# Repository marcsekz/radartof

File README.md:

## Fun stuff:
- USB descriptor will always fail on CM4, as that core does not have access to the memory area containing the device ID. Mitigated with fixed ID.
- UART4 is connected in reverse to STDC14 debug connector (whoopsie)
-

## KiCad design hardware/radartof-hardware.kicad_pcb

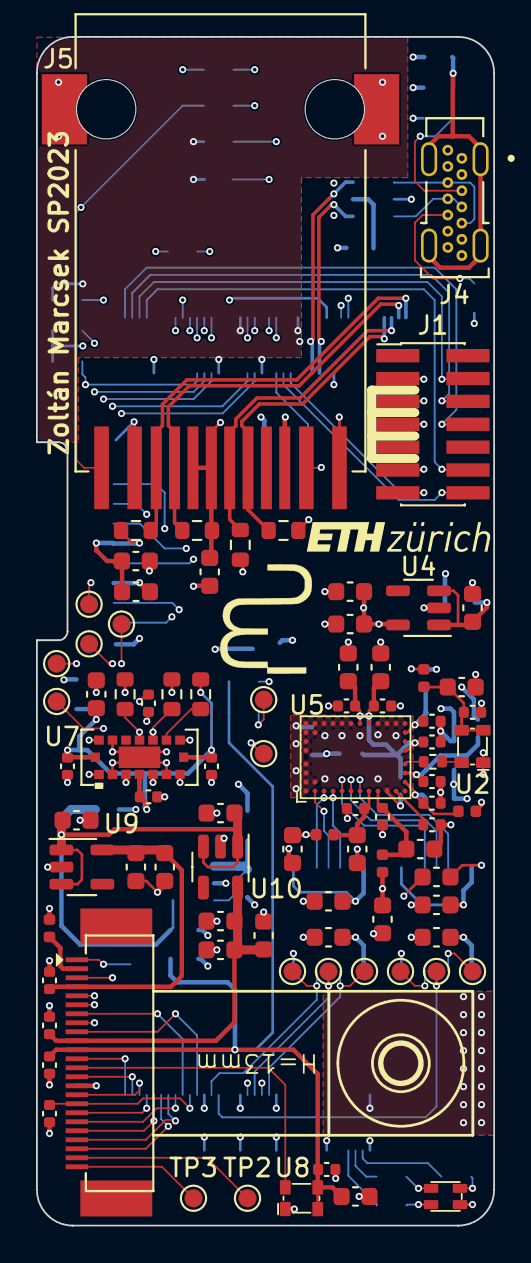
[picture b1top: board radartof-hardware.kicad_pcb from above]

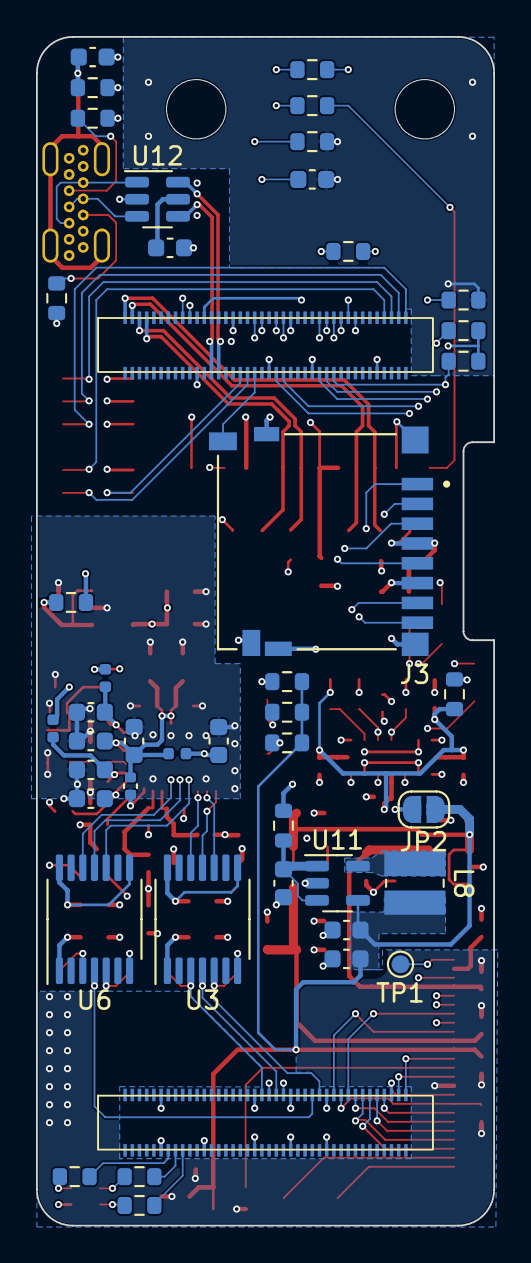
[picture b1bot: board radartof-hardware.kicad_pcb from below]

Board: 6 copper layers, 25.4 x 66.0 mm, 130 parts (44 on the bottom side), 95 nets.

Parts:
C1, C4, C12, C18, C19, C26, C27, C32, C36, C37, C38, C42, C43, C44, C46, C47, C48, C50, C61: 10u; C_0603_1608Metric
C2, C5, C7, C9, C14, C16, C21, C23, C45: 1u; C_0603_1608Metric
C3, C6, C8, C10, C13, C15, C17, C20, C22, C24: 10n; C_0402_1005Metric
C11, C34, C49, C51, C53, C57, C58, C59, C60: 100n; C_0603_1608Metric
C25: 470n; C_0402_1005Metric
C28: 4u7; C_0603_1608Metric
C29, C30, C31, C33, C39, C40, C41, C55: 100n; C_0402_1005Metric
C35: 22p; C_0402_1005Metric
C54: 1n; C_0603_1608Metric
D1: Würth 150066M153000; Würth_150066M153000
J1: Debug; PinHeader_2x07_P1.27mm_Vertical_SMD
J2: Camera; OV2640FSL
J3: 1140084168; AMPHENOL_1140084168
J4: FS USB; MOLEX_216989-0001
J5: J3026G01DNLT; PE_J3026G01DNLT
JP2: 3v3 Select; SolderJumper-2_P1.3mm_Open_RoundedPad1.0x1.5mm
L1, L2, L3, L4, L5, L6, L7, L9: BLM15PX471SZ1D; L_0402_1005Metric
L8: 74438336022; L_Wuerth_MAPI-3020
R1: 150; R_0402_1005Metric
R2, R3, R10, R11: 2k2; R_0603_1608Metric
R4, R5, R6, R7: 47k; R_0603_1608Metric
R8, R9: 10k; R_0603_1608Metric
R12, R13, R14, R15: 49.9; R_0603_1608Metric
R16, R17: 5k1; R_0603_1608Metric
R18, R19, R26: 470; R_0603_1608Metric
R20: 1M; R_0603_1608Metric
R21, R22, R23, R24: 0; R_0603_1608Metric
R25: 1k; R_0603_1608Metric
R27: 220; R_0603_1608Metric
TP1: Strobe; TestPoint_Pad_D1.0mm
TP2: Vmotor; TestPoint_Pad_D1.0mm
TP3: GNDmotor; TestPoint_Pad_D1.0mm
TP4: MOSI; TestPoint_Pad_D1.0mm
TP5: SCK; TestPoint_Pad_D1.0mm
TP6: RADAR_INT; TestPoint_Pad_D1.0mm
TP7: NSS; TestPoint_Pad_D1.0mm
TP8: RADAR_nRST; TestPoint_Pad_D1.0mm
TP9: MISO; TestPoint_Pad_D1.0mm
TP10: TOF_LPn; TestPoint_Pad_D1.0mm
TP11: SCL3; TestPoint_Pad_D1.0mm
TP12: SDA3; TestPoint_Pad_D1.0mm
TP13: TOF_INT; TestPoint_Pad_D1.0mm
TP14: TOF_RST; TestPoint_Pad_D1.0mm
TP15: SDA1; TestPoint_Pad_D1.0mm
TP16: SCL1; TestPoint_Pad_D1.0mm
U1: DF40HC(3.5)-80DS-0.4V(51); MODULE_ABX00042_NOSCREWS
U2: KC2016Z80.0000; KC2016Z
U3, U6: TXU0304; TSSOP-14_4.4x5mm_P0.65mm
U4: TLV74318 SOT23-5; SOT-23-5
U5: BGT60UTR13DAiP
U7: VL53L5CXV0GC/1; VL53L5CXV0GC&slash_1
U8: KC2016Z24.0000; KC2016Z
U9: TLV74328 SOT23-5; SOT-23-5
U10: TLV74315 SOT23-5; SOT-23-5
U11: LM3671MF-3.3; TSOT-23-5
U12: USBLC6-2SC6; SOT-23-6

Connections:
+1V5: C40.1, C43.1, C44.1, C45.1, J2.10, U10.5 (OUT)
+1V8: C4.1, C11.1, C18.1, C27.1, C58.1, C60.1, C61.1, L2.1, L3.1, L4.1, L5.1, L6.1, L7.1, U3.8 (OE), U3.14 (VCCB), U4.5 (OUT), U6.8 (OE), U6.14 (VCCB)
+2V8: C37.1, C38.1, C39.1, J2.4, U9.5 (OUT)
+3.3V: C49.1, C50.1, C51.1, C55.1, D1.4 (A), J1.3 (VCC), J3.4 (VDD), J5.5 (TCT), J5.6 (RCT), J5.12, JP2.2 (B), R2.1, R3.1, R4.1, R5.1, R12.1, R13.1, R14.1, R15.1, R23.1, R24.1, U1.J1_72 (V-SDCARD), U1.J2_23 (VCC/+3V3), U1.J2_34 (VCC), U1.J2_43 (VCC/+3V3), U1.J2_69 (VCC/+3V3)
+5V: R22.1, U1.J1_23 (USB1_VBUS)
/Camera/5v_tof: C46.1, R22.2, U11.1 (Vin), U11.3 (EN)
/Camera/CAM_CK: C35.1, J2.17, U1.J2_20 (CAM_CLK)
/Camera/CAM_D0: J2.19, U1.J2_16 (CAM_D0)
/Camera/CAM_D1: J2.21, U1.J2_14 (CAM_D1)
/Camera/CAM_D2: J2.22, U1.J2_12 (CAM_D2)
/Camera/CAM_D3: J2.20, U1.J2_10 (CAM_D3)
/Camera/CAM_D4: J2.18, U1.J2_8 (CAM_D4)
/Camera/CAM_D5: J2.16, U1.J2_6 (CAM_D5)
/Camera/CAM_D6: J2.14, U1.J2_4 (CAM_D6)
/Camera/CAM_D7: J2.12, U1.J2_2 (CAM_D7)
/Camera/CAM_HS: J2.9, U1.J2_22 (CAM_HS)
/Camera/CAM_PWDN: J2.8, R9.1, U1.J1_37 (UART1_RTS)
/Camera/CAM_VS: J2.7, U1.J2_18 (CAM_VS)
/Camera/CAM_nRST: C34.1, J2.6, R8.2, U1.J1_39 (UART1_CTS)
/Camera/GNDMotor: J2.24, TP3.1
/Camera/I2C1_SCL: J2.5, R11.2, TP16.1, U1.J1_45 (I2C1_SCL)
/Camera/I2C1_SDA: J2.3, R10.2, TP15.1, U1.J1_43 (I2C1_SDA)
/Camera/LX: L8.1, U11.5 (SW)
/Camera/STROBE: J2.1, TP1.1
/Camera/Vmotor: J2.23, TP2.1
/Camera/XCLK: J2.13, U8.3 (CLK)
/Connectors/ETH_A+: J5.3 (TD+), R12.2, U1.J1_1 (ETH_A+)
/Connectors/ETH_A-: J5.4 (TD-), R13.2, U1.J1_3 (ETH_A-)
/Connectors/ETH_B+: J5.7 (RD+), R14.2, U1.J1_5 (ETH_B+)
/Connectors/ETH_B-: J5.8 (RD-), R15.2, U1.J1_7 (ETH_B-)
/Connectors/ETH_LED1: R19.1, U1.J1_17 (ETH_L1)
/Connectors/ETH_LED2: R18.1, U1.J1_19 (ETH_L2)
/Connectors/USB_FS+: U1.J1_26 (USB0_D+), U12.4 (I/O2)
/Connectors/USB_FS-: U1.J1_28 (USB0_D-), U12.6 (I/O1)
/Connectors/USB_Shield: C54.1, J4.S1 (SHIELD), R20.1
/Connectors/conn_USB+: J4.A7 (D-), J4.B7 (D-), U12.1 (I/O1)
/Connectors/conn_USB-: J4.A6 (D+), J4.B6 (D+), U12.3 (I/O2)
/Portenta/CATB: D1.3 (BK), R27.2
/Portenta/CATG: D1.2 (GK), R26.2
/Portenta/CATR: D1.1 (RK), R25.2
/Portenta/I2C3_SCL: R2.2, TP11.1, U1.J1_46 (I2C0_SCL), U7.C4 (SCL)
/Portenta/I2C3_SDA: R3.2, TP12.1, U1.J1_44 (I2C0_SDA), U7.C3 (SDA)
/Portenta/RADAR_INT: TP6.1, U1.J2_26 (UART2_TX), U3.5 (A4Y)
/Portenta/RADAR_nRST: TP8.1, U1.J2_28 (UART2_RX), U6.4 (A3)
/Portenta/SDC_CD: J3.9 (DET_B), U1.J1_38 (UART0_RTS)
/Portenta/SDC_CLK: J3.5 (CLK), U1.J1_55 (SDC_CLK)
/Portenta/SDC_CMD: J3.3 (CMD), U1.J1_57 (SDC_CMD)
/Portenta/SDC_D0: J3.7 (DAT0), U1.J1_59 (SDC_D0)
/Portenta/SDC_D1: J3.8 (DAT1), U1.J1_61 (SDC_D1)
/Portenta/SDC_D2: R21.1, U1.J1_63 (SDC_D2)
/Portenta/SDC_D3: J3.2 (DAT3/CD), U1.J1_65 (SDC_D3)
/Portenta/SPI2_MISO: TP9.1, U1.J2_40 (SPI1_MISO), U6.5 (A4Y)
/Portenta/SPI2_MOSI: TP4.1, U1.J2_42 (SPI1_MOSI), U3.3 (A2)
/Portenta/SPI2_NSS: TP7.1, U1.J2_36 (SPI1_CS), U6.3 (A2)
/Portenta/SPI2_SCK: TP5.1, U1.J2_38 (SPI1_CK), U3.4 (A3)
/Portenta/SWCLK: J1.6 (JCLK/SWCLK), U1.J1_77 (SWCK)
/Portenta/SWDIO: J1.4 (JTMS/SWDIO), U1.J1_75 (SWDIO)
/Portenta/SWO: J1.8 (JTDO/SWO), U1.J1_79 (SWO)
/Portenta/TOF_INT: R4.2, TP13.1, U1.J1_58 (I2S_WS), U7.A3 (INT)
/Portenta/TOF_LPn: R5.2, TP10.1, U1.J1_60 (I2S_DI), U7.A5 (LPn)
/Portenta/TOF_RST: R7.1, TP14.1, U1.J1_56 (I2S_MCK), U7.A1 (I2C_RST)
/Portenta/UART4_RX: J1.14 (VCP_TX), U1.J1_36 (UART0_RX)
/Portenta/UART4_TX: J1.13 (VCP_RX), U1.J1_34 (UART0_TX)
/Portenta/nLEDB: R27.1, U1.J2_67 (PWM_5)
/Portenta/nLEDG: R26.1, U1.J2_65 (PWM_4)
/Portenta/nLEDR: R25.1, U1.J2_63 (PWM_3)
/Portenta/nRST: J1.12 (~RST), U1.J1_73 (~RESET)
/Radar/80mhz: R1.1, U2.3 (CLK)
/Radar/INT_1V8: U3.10 (B4), U5.C1 (IRQ)
/Radar/MISO_1V8: U5.E1 (MISO), U6.10 (B4)
/Radar/MOSI_1V8: U3.12 (B2Y), U5.D1 (MOSI)
/Radar/NSS_1V8: U5.G1 (~CS), U6.12 (B2Y)
/Radar/OSC_CLK: R1.2, U5.M4 (OSC_CLK)
/Radar/RST_1V8: U5.F1 (RST), U6.11 (B3Y)
/Radar/SCK_1V8: U3.11 (B3Y), U5.B1 (CLK)
/Radar/VDD_A: C12.1, C13.1, L4.2, U5.J1 (VDD_{A})
/Radar/VDD_D: C5.1, C6.1, L2.2, U5.H1 (VDD_{D})
/Radar/VDD_LF: C2.1, C3.1, L1.2, U5.M2 (VDD_{LF})
/Radar/VDD_PLL: C14.1, C15.1, L5.2, U5.M3 (VDD_{PLL})
/Radar/VDD_RF: C7.1, C8.1, C16.1, C17.1, C19.1, C20.1, C23.1, C24.1, L6.2, U5.G8 (VDD_{RF}), U5.H8 (VDD_{RF}), U5.M5 (VDD_{RF})
/Radar/VDD_VCO: C21.1, C22.1, L7.2, U5.M7 (VDD_{VCO})
/Radar/V_AREF: C25.1, U5.L1 (V_{AREF})
/Radar/V_OSC: C9.1, C10.1, L3.2, U2.1 (INH), U2.4 (VCC)
/ToF Sensor/RSVD6: R6.2, U7.C2 (RSVD6)
GND: C1.2, C2.2, C3.2, C4.2, C5.2, C6.2, C7.2, C8.2, C9.2, C10.2, C11.2, C12.2, C13.2, C14.2, C15.2, C16.2, C17.2, C18.2, C19.2, C20.2, C21.2, C22.2, C23.2, C24.2, C25.2, C26.2, C27.2, C28.2, C29.2, C30.2, C31.2, C32.2, C33.2, C34.2, C35.2, C36.2, C37.2, C38.2, C39.2, C40.2, C41.2, C42.2, C43.2, C44.2, C45.2, C46.2, C47.2, C48.2, C49.2, C50.2, C51.2, C53.2, C54.2, C55.2, C57.2, C58.2, C59.2, C60.2, C61.2, J1.5 (GND), J1.7 (GND), J1.11 (GNDDetect), J2.15, J3.6 (VSS), J3.10 (DET_A), J3.11 (SHIELD), J4.A1 (GND), J4.A12 (GND), J4.B1 (GND), J4.B12 (GND), J5.2, J5.10, J5.S1 (SHIELD), J5.S2 (SHIELD), L9.1, R7.2, R9.2, R16.1, R17.1, R20.2, U1.J1_22 (GND), U1.J1_31 (GND), U1.J1_42 (GND), U1.J1_47 (GND), U1.J1_54 (GND), U1.J2_24 (GND_1), U1.J2_33 (GND_1), U1.J2_44 (GND_1), U1.J2_57 (GND_1), U1.J2_70 (GND_1), U2.2 (GND), U3.7 (GND), U4.2 (GND), U5.A1 (VSS_{RF}), U5.A2 (VSS_{D}), U5.A3 (VSS_{D}), U5.A4 (VSS_{RF}), U5.A5 (VSS_{RF}), U5.A6 (VSS_{RF}), U5.A7 (VSS_{RF}), U5.A8 (VSS_{RF}), U5.B2 (VSS_{RF}), U5.B7 (VSS_{RF}), U5.B8 (VSS_{RF}), U5.C8 (VSS_{RF}), U5.D8 (VSS_{RF}), U5.E8 (VSS_{RF}), U5.F8 (VSS_{RF}), U5.J8 (VSS_{RF}), U5.K1 (VSS_{A}), U5.K8 (VSS_{RF}), U5.L8 (VSS_{RF}), U5.M1 (VSS_{RF}), U5.M8 (VSS_{RF}), U6.7 (GND), U7.A2 (RSVD4), U7.A6 (RSVD1), U7.A7 (RSVD2), U7.B4 (THERMAL_PAD), U7.C1 (GND), U7.C6 (RSVD3), U7.C7 (GND), U8.2 (GND), U9.2 (GND), U10.2 (GND), U11.2 (GND), U12.2 (GND)
GNDA: J2.2, L9.2
unnamed: J3.1 (DAT2), R21.2
unnamed: J4.A5 (CC1), R16.2
unnamed: J4.B5 (CC2), R17.2
unnamed: J5.1, R18.2
unnamed: J5.11, R19.2
unnamed: C53.1, U12.5 (VBUS)
VCAM: C32.1, C33.1, C36.1, C41.1, C42.1, C47.1, C48.1, J2.11, JP2.1 (A), L8.2, R8.1, R10.1, R11.1, U8.1 (INH), U8.4 (VCC), U9.1 (IN), U9.3 (EN), U10.1 (IN), U10.3 (EN), U11.4 (FB)
VTOF: C28.1, C29.1, C30.1, C31.1, R6.1, R24.2, U7.A4 (IOVDD), U7.B1 (AVDD), U7.B7 (AVDD)
Vradar: C1.1, C26.1, C57.1, C59.1, L1.1, R23.2, U3.1 (VCCA), U4.1 (IN), U4.3 (EN), U6.1 (VCCA)

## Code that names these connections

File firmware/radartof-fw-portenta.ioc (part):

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Mcu.Name=STM32H747XIHx
Mcu.Package=TFBGA240
Mcu.UserName=STM32H747XIHx
PA0.GPIOParameters=PinAttribute
PA0.Mode=Asynchronous
PA0.PinAttribute=CortexM4
PA0.Signal=UART4_TX
PA1.GPIOParameters=GPIO_Speed,PinAttribute
PA1.GPIO_Speed=GPIO_SPEED_FREQ_VERY_HIGH
PA1.Mode=RMII
PA1.PinAttribute=CortexM7
PA1.Signal=ETH_REF_CLK
PA11.GPIOParameters=PinAttribute
PA11.Mode=Device_Only
PA11.PinAttribute=CortexM4
PA11.Signal=USB_OTG_FS_DM
PA12.GPIOParameters=PinAttribute
PA12.Mode=Device_Only
PA12.PinAttribute=CortexM4
PA12.Signal=USB_OTG_FS_DP
PA13\ (JTMS/SWDIO).GPIOParameters=PinAttribute
PA13\ (JTMS/SWDIO).Mode=Serial_Wire
PA13\ (JTMS/SWDIO).PinAttribute=CortexM7
PA13\ (JTMS/SWDIO).Signal=DEBUG_JTMS-SWDIO
PA14\ (JTCK/SWCLK).GPIOParameters=PinAttribute
PA14\ (JTCK/SWCLK).Mode=Serial_Wire
PA14\ (JTCK/SWCLK).PinAttribute=CortexM7
PA14\ (JTCK/SWCLK).Signal=DEBUG_JTCK-SWCLK
PA2.GPIOParameters=GPIO_Speed,PinAttribute
PA2.GPIO_Speed=GPIO_SPEED_FREQ_VERY_HIGH
PA2.Mode=RMII
PA2.PinAttribute=CortexM7
PA2.Signal=ETH_MDIO
PA3.GPIOParameters=PinAttribute
PA3.Mode=Device_HS
PA3.PinAttribute=CortexM7
PA3.Signal=USB_OTG_HS_ULPI_D0
PA4.GPIOParameters=PinAttribute
PA4.Mode=Slave_8_bits_External_Synchro
PA4.PinAttribute=CortexM4
PA4.Signal=DCMI_HSYNC
PA5.GPIOParameters=PinAttribute
PA5.Mode=Device_HS
PA5.PinAttribute=CortexM7
PA5.Signal=USB_OTG_HS_ULPI_CK
PA6.GPIOParameters=PinAttribute
PA6.Mode=Slave_8_bits_External_Synchro
PA6.PinAttribute=CortexM4
PA6.Signal=DCMI_PIXCLK
PA7.GPIOParameters=GPIO_Speed,PinAttribute
PA7.GPIO_Speed=GPIO_SPEED_FREQ_VERY_HIGH
PA7.Mode=RMII
PA7.PinAttribute=CortexM7
PA7.Signal=ETH_CRS_DV
PA8.GPIOParameters=GPIO_Label,PinAttribute
PA8.GPIO_Label=TOF_PWREN
PA8.PinAttribute=Free
PA8.Signal=GPIO_Output
PB0.GPIOParameters=PinAttribute
PB0.Mode=Device_HS
PB0.PinAttribute=CortexM7
PB0.Signal=USB_OTG_HS_ULPI_D1
PB1.GPIOParameters=PinAttribute
PB1.Mode=Device_HS
PB1.PinAttribute=CortexM7
PB1.Signal=USB_OTG_HS_ULPI_D2
PB10.GPIOParameters=PinAttribute
PB10.Mode=Device_HS
PB10.PinAttribute=CortexM7
PB10.Signal=USB_OTG_HS_ULPI_D3
PB11.GPIOParameters=PinAttribute
PB11.Mode=Device_HS
PB11.PinAttribute=CortexM7
PB11.Signal=USB_OTG_HS_ULPI_D4
PB12.GPIOParameters=PinAttribute
PB12.Mode=Device_HS
PB12.PinAttribute=CortexM7
PB12.Signal=USB_OTG_HS_ULPI_D5
PB13.GPIOParameters=PinAttribute
PB13.Mode=Device_HS
PB13.PinAttribute=CortexM7
PB13.Signal=USB_OTG_HS_ULPI_D6
PB14.GPIOParameters=PinAttribute
PB14.Mode=SD_4_bits_Wide_bus
PB14.PinAttribute=CortexM7
PB14.Signal=SDMMC2_D0
PB15.GPIOParameters=PinAttribute
PB15.Mode=SD_4_bits_Wide_bus
PB15.PinAttribute=CortexM7
PB15.Signal=SDMMC2_D1
PB3\ (JTDO/TRACESWO).GPIOParameters=PinAttribute
PB3\ (JTDO/TRACESWO).Mode=SD_4_bits_Wide_bus
PB3\ (JTDO/TRACESWO).PinAttribute=CortexM7
PB3\ (JTDO/TRACESWO).Signal=SDMMC2_D2
PB4\ (NJTRST).GPIOParameters=PinAttribute
PB4\ (NJTRST).Mode=SD_4_bits_Wide_bus
PB4\ (NJTRST).PinAttribute=CortexM7
PB4\ (NJTRST).Signal=SDMMC2_D3
PB5.GPIOParameters=PinAttribute
PB5.Mode=Device_HS
PB5.PinAttribute=CortexM7
PB5.Signal=USB_OTG_HS_ULPI_D7
PB6.GPIOParameters=PinAttribute
PB6.Mode=I2C
PB6.PinAttribute=CortexM7
PB6.Signal=I2C1_SCL
PB7.GPIOParameters=PinAttribute
PB7.Mode=I2C
PB7.PinAttribute=CortexM7
PB7.Signal=I2C1_SDA
PB9.ContextOwner=CortexM4
PB9.GPIOParameters=GPIO_Label,PinAttribute
PB9.GPIO_Label=TOF_INT
PB9.PinAttribute=CortexM4
PB9.Signal=GPIO_Input
PC0.GPIOParameters=PinAttribute
PC0.Mode=Device_HS
PC0.PinAttribute=CortexM7
PC0.Signal=USB_OTG_HS_ULPI_STP
PC1.GPIOParameters=GPIO_Speed,PinAttribute
PC1.GPIO_Speed=GPIO_SPEED_FREQ_VERY_HIGH
PC1.Mode=RMII
PC1.PinAttribute=CortexM7
PC1.Signal=ETH_MDC
PC14-OSC32_IN\ (OSC32_IN).GPIOParameters=PinAttribute
PC14-OSC32_IN\ (OSC32_IN).Mode=LSE-External-Clock-Source
PC14-OSC32_IN\ (OSC32_IN).PinAttribute=Free
PC14-OSC32_IN\ (OSC32_IN).Signal=RCC_OSC32_IN
PC2.GPIOParameters=PinAttribute
PC2.Mode=Full_Duplex_Master
PC2.PinAttribute=CortexM4
PC2.Signal=SPI2_MISO
PC3.GPIOParameters=PinAttribute
PC3.Mode=Full_Duplex_Master
PC3.PinAttribute=CortexM4
PC3.Signal=SPI2_MOSI
PC4.GPIOParameters=GPIO_Speed,PinAttribute
PC4.GPIO_Speed=GPIO_SPEED_FREQ_VERY_HIGH
PC4.Mode=RMII
PC4.PinAttribute=CortexM7
PC4.Signal=ETH_RXD0
PC5.GPIOParameters=GPIO_Speed,PinAttribute
PC5.GPIO_Speed=GPIO_SPEED_FREQ_VERY_HIGH
PC5.Mode=RMII
PC5.PinAttribute=CortexM7
PC5.Signal=ETH_RXD1
PD0.GPIOParameters=PinAttribute
PD0.PinAttribute=CortexM7
PD0.Signal=FMC_D2_DA2
PD1.GPIOParameters=PinAttribute
PD1.PinAttribute=CortexM7
PD1.Signal=FMC_D3_DA3
PD10.GPIOParameters=PinAttribute
PD10.PinAttribute=CortexM7
PD10.Signal=FMC_D15_DA15
PD11.GPIOParameters=PinAttribute
PD11.Mode=Single Bank 1
PD11.PinAttribute=CortexM7
PD11.Signal=QUADSPI_BK1_IO0
PD12.GPIOParameters=PinAttribute
PD12.Mode=Single Bank 1
PD12.PinAttribute=CortexM7
PD12.Signal=QUADSPI_BK1_IO1
PD13.GPIOParameters=PinAttribute
PD13.Mode=Single Bank 1
PD13.PinAttribute=CortexM7
PD13.Signal=QUADSPI_BK1_IO3
PD14.GPIOParameters=PinAttribute
PD14.PinAttribute=CortexM7
PD14.Signal=FMC_D0_DA0
PD15.GPIOParameters=PinAttribute
PD15.PinAttribute=CortexM7
PD15.Signal=FMC_D1_DA1
PD3.GPIOParameters=GPIO_Label,PinAttribute
PD3.GPIO_Label=TOF_RST
PD3.PinAttribute=Free
PD3.Signal=GPIO_Output
PD6.GPIOParameters=PinAttribute
PD6.Mode=SD_4_bits_Wide_bus
PD6.PinAttribute=CortexM7
PD6.Signal=SDMMC2_CK
PD7.GPIOParameters=PinAttribute
PD7.Mode=SD_4_bits_Wide_bus
PD7.PinAttribute=CortexM7
PD7.Signal=SDMMC2_CMD
PD8.GPIOParameters=PinAttribute
PD8.PinAttribute=CortexM7
PD8.Signal=FMC_D13_DA13
PD9.GPIOParameters=PinAttribute
PD9.PinAttribute=CortexM7
PD9.Signal=FMC_D14_DA14
PE0.GPIOParameters=PinAttribute
PE0.PinAttribute=CortexM7
PE0.Signal=FMC_NBL0
PE1.GPIOParameters=PinAttribute
PE1.PinAttribute=CortexM7
PE1.Signal=FMC_NBL1
PE10.GPIOParameters=PinAttribute
PE10.PinAttribute=CortexM7
PE10.Signal=FMC_D7_DA7
PE11.GPIOParameters=PinAttribute
PE11.PinAttribute=CortexM7
PE11.Signal=FMC_D8_DA8
PE12.GPIOParameters=PinAttribute
PE12.PinAttribute=CortexM7
PE12.Signal=FMC_D9_DA9
PE13.GPIOParameters=PinAttribute
PE13.PinAttribute=CortexM7
PE13.Signal=FMC_D10_DA10
PE14.GPIOParameters=PinAttribute
PE14.PinAttribute=CortexM7
PE14.Signal=FMC_D11_DA11
PE15.GPIOParameters=PinAttribute
PE15.PinAttribute=CortexM7
PE15.Signal=FMC_D12_DA12
PE7.GPIOParameters=PinAttribute
PE7.PinAttribute=CortexM7
PE7.Signal=FMC_D4_DA4
PE8.GPIOParameters=PinAttribute
PE8.PinAttribute=CortexM7
PE8.Signal=FMC_D5_DA5
PE9.GPIOParameters=PinAttribute
PE9.PinAttribute=CortexM7
PE9.Signal=FMC_D6_DA6
PF0.GPIOParameters=PinAttribute
PF0.PinAttribute=CortexM7
PF0.Signal=FMC_A0
PF1.GPIOParameters=PinAttribute
PF1.PinAttribute=CortexM7
PF1.Signal=FMC_A1
PF10.GPIOParameters=PinAttribute
PF10.Mode=Single Bank 1
PF10.PinAttribute=CortexM7
PF10.Signal=QUADSPI_CLK
PF11.GPIOParameters=PinAttribute
PF11.PinAttribute=CortexM7
PF11.Signal=FMC_SDNRAS
PF12.GPIOParameters=PinAttribute
PF12.PinAttribute=CortexM7
PF12.Signal=FMC_A6
PF13.GPIOParameters=PinAttribute
PF13.PinAttribute=CortexM7
PF13.Signal=FMC_A7
PF14.GPIOParameters=PinAttribute
PF14.PinAttribute=CortexM7
PF14.Signal=FMC_A8
PF15.GPIOParameters=PinAttribute
PF15.PinAttribute=CortexM7
PF15.Signal=FMC_A9
PF2.GPIOParameters=PinAttribute
PF2.PinAttribute=CortexM7
PF2.Signal=FMC_A2
PF3.GPIOParameters=PinAttribute
PF3.PinAttribute=CortexM7
PF3.Signal=FMC_A3
PF4.GPIOParameters=PinAttribute
PF4.PinAttribute=CortexM7
PF4.Signal=FMC_A4
PF5.GPIOParameters=PinAttribute
PF5.PinAttribute=CortexM7
PF5.Signal=FMC_A5
PF7.GPIOParameters=PinAttribute
PF7.Mode=Single Bank 1
PF7.PinAttribute=CortexM7
PF7.Signal=QUADSPI_BK1_IO2
PG0.GPIOParameters=PinAttribute
PG0.PinAttribute=CortexM7
PG0.Signal=FMC_A10
PG1.GPIOParameters=PinAttribute
PG1.PinAttribute=CortexM7
PG1.Signal=FMC_A11
PG11.GPIOParameters=GPIO_Speed,PinAttribute
PG11.GPIO_Speed=GPIO_SPEED_FREQ_VERY_HIGH
PG11.Mode=RMII
PG11.PinAttribute=CortexM7
PG11.Signal=ETH_TX_EN
PG12.GPIOParameters=GPIO_Speed,PinAttribute
PG12.GPIO_Speed=GPIO_SPEED_FREQ_VERY_HIGH
PG12.Mode=RMII
PG12.PinAttribute=CortexM7
PG12.Signal=ETH_TXD1
PG13.GPIOParameters=GPIO_Speed,PinAttribute
PG13.GPIO_Speed=GPIO_SPEED_FREQ_VERY_HIGH
PG13.Mode=RMII
PG13.PinAttribute=CortexM7
PG13.Signal=ETH_TXD0
PG14.ContextOwner=CortexM4
PG14.GPIOParameters=GPIO_Label,PinAttribute
PG14.GPIO_Label=RADAR_INT
PG14.PinAttribute=CortexM4
PG14.Signal=GPIO_Input
PG15.GPIOParameters=PinAttribute
PG15.PinAttribute=CortexM7
PG15.Signal=FMC_SDNCAS
PG4.GPIOParameters=PinAttribute
PG4.PinAttribute=CortexM7
PG4.Signal=FMC_A14_BA0
PG5.GPIOParameters=PinAttribute
PG5.PinAttribute=CortexM7
PG5.Signal=FMC_A15_BA1
PG6.GPIOParameters=PinAttribute
PG6.Mode=Single Bank 1
PG6.PinAttribute=CortexM7
PG6.Signal=QUADSPI_BK1_NCS
PG8.GPIOParameters=PinAttribute
PG8.PinAttribute=CortexM7
PG8.Signal=FMC_SDCLK
PG9.ContextOwner=CortexM4
PG9.GPIOParameters=GPIO_Label,PinAttribute
PG9.GPIO_Label=RADAR_nRST
PG9.PinAttribute=CortexM4
PG9.Signal=GPIO_Output
PH0-OSC_IN\ (PH0).GPIOParameters=PinAttribute
PH0-OSC_IN\ (PH0).Mode=HSE-External-Clock-Source
PH0-OSC_IN\ (PH0).PinAttribute=Free

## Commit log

2023-04-14 Init
2023-04-14 Add schematic pdf
2023-04-16 final-ish schematic
2023-04-24 Finished routing
2023-04-24 Update CubeMX config
2023-04-24 Add PCB PDF export
2023-04-25 Add testpoints, 0ohm, led, logos
2023-04-26 Final fixes, manufacturing
2023-05-08 Started firmware
2023-05-08 Manufacturing
2023-05-08 Backup on-board firmware, I2C trace
2023-05-08 Fix GPIO inits
2023-05-08 Use HSI until HSE enabled
2023-05-08 WIP bootup
2023-05-23 ToF demo working
2023-06-06 Ethernet working, add drivers for radar and camera
2023-06-14 still with half of the printing stuff
2023-06-16 Ignore firmware2
2023-06-16 Implement ToF over UDP
2023-06-16 Add scripts to visualize and save tof data
2023-06-21 Fix invalid pixels, add logging to tofrender
2023-06-26 Add dataset
2023-06-26 Removed firmware2 from git
2023-06-26 Fix radar footprint

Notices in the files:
parts and their libraries:
Copyright 2021 Accelerated Designs. All rights reserved.
